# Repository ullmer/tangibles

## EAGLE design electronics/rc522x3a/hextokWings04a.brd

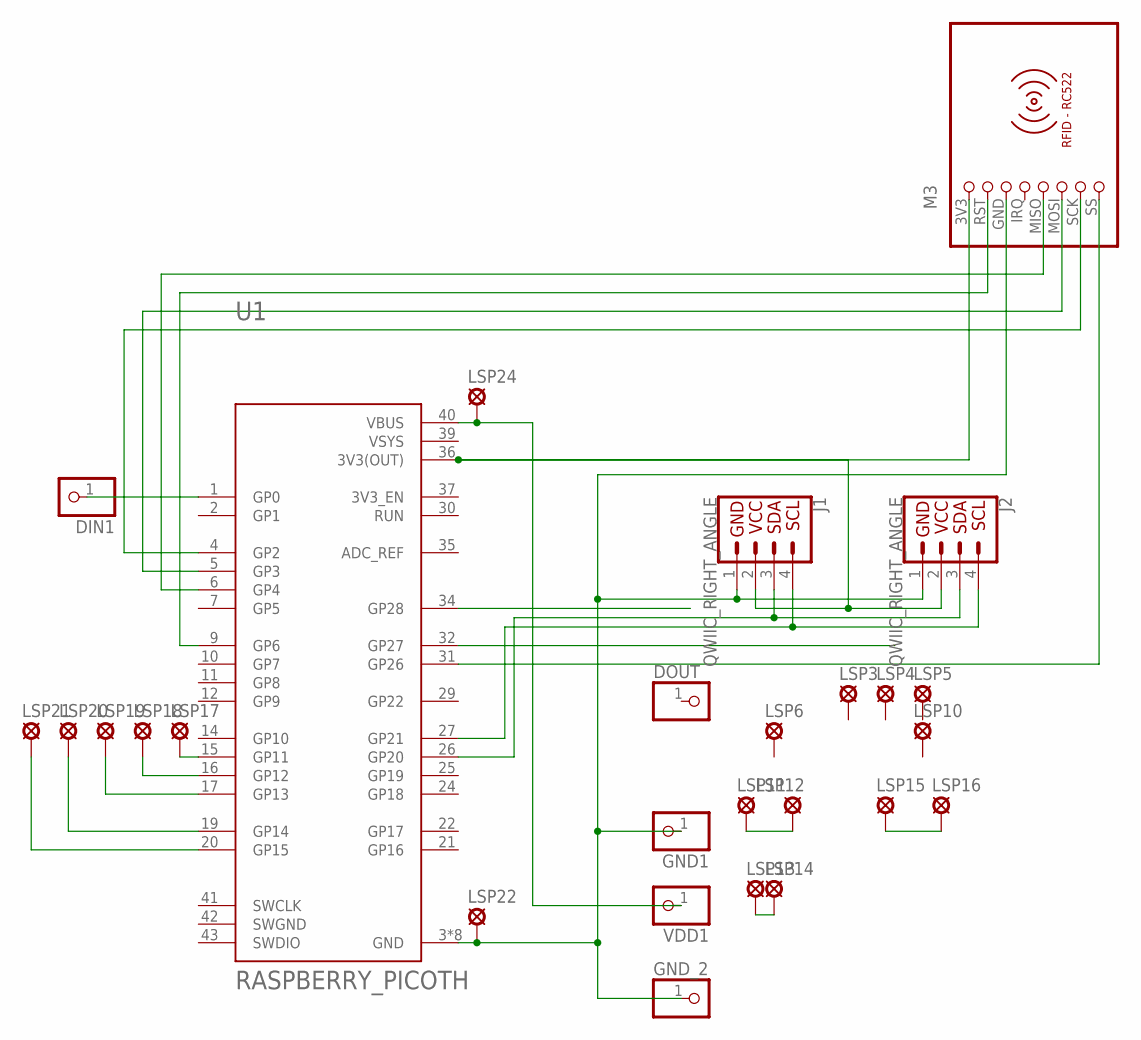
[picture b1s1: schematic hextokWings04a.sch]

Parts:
DIN1: PINHD-1X1CB; 1X01-CLEANBIG
DOUT: PINHD-1X1CB; 1X01-CLEANBIG
GND1: PINHD-1X1CB; 1X01-CLEANBIG
GND_2: PINHD-1X1CB; 1X01-CLEANBIG
J1, J2: QWIIC_RIGHT_ANGLE; JST04_1MM_RA
LSP3, LSP4, LSP5, LSP6, LSP10, LSP11, LSP12, LSP13, LSP14, LSP15, LSP16, LSP17, LSP18, LSP19, LSP20, LSP21, LSP22, LSP24: LSP10
M3: RFID-RC522
U1: RASPBERRY_PICOTH; PICO-PKG-TH
VDD1: PINHD-1X1CB; 1X01-CLEANBIG

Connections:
unnamed: J1.2, J2.2, M3.3V3 (1), U1.36 (3V3(OUT))
unnamed: M3.MOSI (6), U1.5 (GP3)
unnamed: M3.SCK (7), U1.4 (GP2)
unnamed: M3.RST (2), U1.9 (GP6)
unnamed: M3.SS (8), U1.31 (GP26)
unnamed: DIN1.1, U1.1 (GP0)
unnamed: LSP24.MP, U1.40 (VBUS), VDD1.1
unnamed: M3.MISO (5), U1.6 (GP4)
unnamed: LSP11.MP, LSP12.MP
unnamed: LSP13.MP, LSP14.MP
unnamed: LSP15.MP, LSP16.MP
unnamed: LSP17.MP, U1.15 (GP11)
unnamed: LSP18.MP, U1.16 (GP12)
unnamed: LSP19.MP, U1.17 (GP13)
unnamed: LSP20.MP, U1.19 (GP14)
unnamed: LSP21.MP, U1.20 (GP15)
unnamed: J1.3, J2.3, U1.26 (GP20)
unnamed: J1.4, J2.4, U1.27 (GP21)
unnamed: GND1.1, GND_2.1, J1.1, J2.1, LSP22.MP, M3.GND (3), U1.3 (GND), U1.8 (GND), U1.13 (GND), U1.18 (GND), U1.23 (GND), U1.28 (GND), U1.33 (GND), U1.38 (GND)
SWGND: U1.42 (SWGND)
VSYS: U1.39 (VSYS)

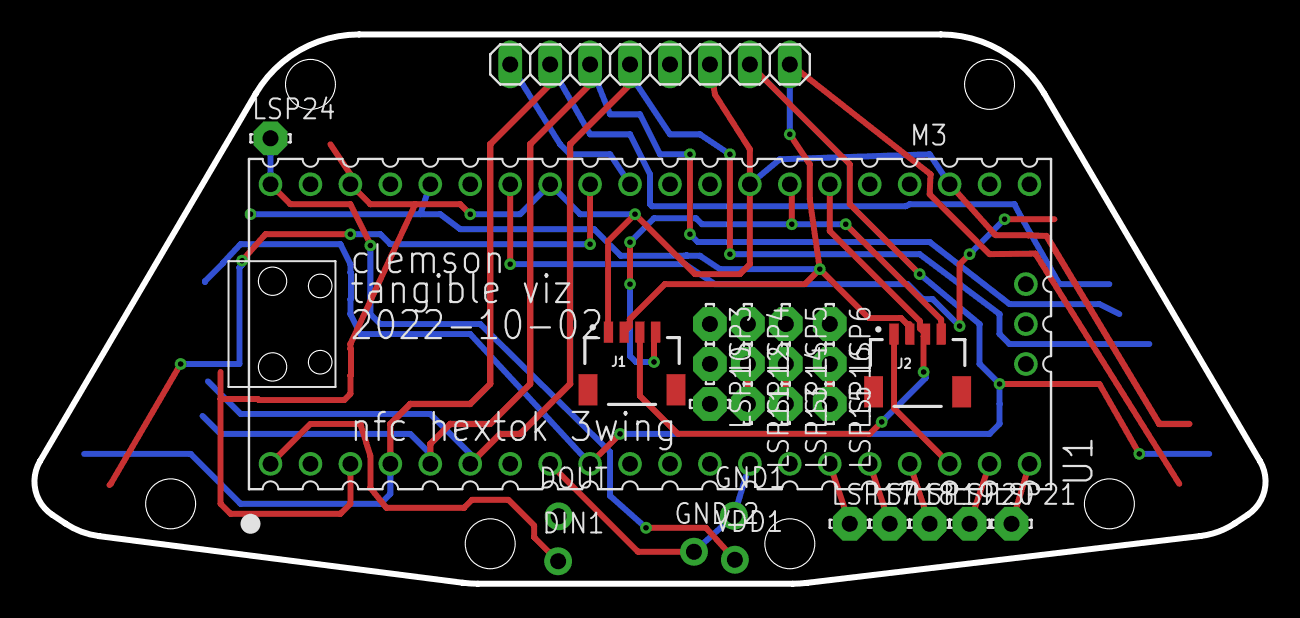
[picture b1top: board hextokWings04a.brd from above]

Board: 2 copper layers, 78.3 x 34.9 mm, 27 parts (0 on the bottom side), 19 nets.

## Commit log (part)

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2025-05-09 moving to exploratory directory, about to rework
2025-05-09 test
2025-05-09 class-descendant evolution
2025-05-09 debugging
2025-05-10 progress
2025-05-10 working
2025-05-12 repeating animation
2025-05-12 seems to be operable
2025-05-12 animated scaling in pygame zero functional. (position settings likely need evolution)
2025-05-12 working to update constructor
2025-05-12 progress with constructor, though seems to break animation
2025-05-12 seems to fix constructor
2025-05-12 seems to fix enoActorScaled constructor
2025-05-13 beginning to add more slider handling
2025-05-14 moving run code to separate file
2025-05-17 Copilot-generated code; untested, migrating between machines to test
2025-05-19 iteration, not yet working
2025-05-19 iterating
2025-05-19 progres
2025-05-19 example aggregations
2025-05-21 debugging midi IDs on an Ubuntu machine (rather than prior win10)
2025-05-21 tweaks
2025-05-21 rect tweak
2025-05-21 Copilot-generated scripts for AVX2 support; seemed to realize ~50% performance acceleration for large Surfaces on an MS Surface Book 2
2025-06-08 port begins
2025-06-08 stub
2025-07-17 warmup
2025-07-17 bau refactoring, mostly layout
2025-07-17 neotrellis entry by copilot, reformatted by bau
2025-07-17 prolog representation of corresponding yaml file
2025-07-17 reminder of package installation
2025-07-17 decimal variations
2025-07-17 visual restructuring
2025-07-17 partitioning underway
2025-07-17 separation of data/facts from transformation/rules
2025-08-21 adding new base class for error management, etc.
2025-08-21 error handling
2025-08-21 different source
2026-01-22 POEMS (Physical Objects with Embedded Memories): Ullmer & Glos, 1995
2026-01-22 Organizational Relations: Brygg Ullmer (fusion of U. Illinois & Interval Research, 1993)
2026-01-22 media browser content (migrated from designThinking)
2026-02-07 small refactoring of mbrowser03.py
2026-02-07 eliminating global
2026-02-27 animation iterations
2026-03-07 first steps]
2026-03-07 first partial pass
2026-03-07 expanded
2026-03-07 Prolog mapping by CoPilot
2026-03-07 fixes
2026-03-07 refactored for plurality of components
2026-03-07 discretizing
2026-03-07 HiLetGo RFID RC522
2026-03-07 HiLetGo RFID-RC522 module Prolog (shadowing equiv YAML)
2026-03-08 more recent mods inaccessible; sigh.
2026-03-16 supporting
2026-03-16 symlink
2026-03-16 top shift animation functioning
2026-03-16 import tweak
2026-03-16 backdrops
2026-03-16 removing temp, sigh
2026-03-16 context on anchors and aliases within YAML
2026-03-17 swiftly evolving
2026-03-17 refactoring
2026-03-17 validation hack
2026-03-18 separating trusted from potentially untrusted elements
2026-03-18 iterations
2026-03-18 first documentation pass
2026-03-18 Update enoPrismsDetails.md — removing more v3s
2026-03-19 tweaking back 03
2026-03-21 replicating 04, beginning to integrate enoPrismsDetails
2026-03-24 Image source (copyright-cleared) and Photoshop 2025-derived variant
2026-03-24 figures and themes toward example
2026-03-24 populating
2026-03-24 renaming, re greater complexity of startup++
2026-03-24 placeholder
2026-03-25 first test
2026-03-25 yaml to prolog transformers
2026-03-25 extending to handle both people and themes
2026-03-25 renaming
2026-03-25 people & themes
2026-03-25 segmenting code
2026-03-25 segmenting, about to wrap into a class
2026-03-25 comment typehinting, in anticipation of mixins
2026-03-25 adding comment typehints
2026-03-25 Enodia people+themes yaml+pgz mixin-augmented classes
2026-03-25 renaming interim
2026-03-25 commented inherited|mixedin fields and methods
2026-03-25 beginning to populate
2026-03-25 try/except
2026-03-25 augmenting
2026-03-25 name abbreviations
2026-03-25 removing
2026-03-25 glyphs
2026-03-25 animation example in class
2026-03-25 moving
2026-03-25 iteration
2026-03-25 100px
2026-03-25 illustrating beginning of abstraction
2026-03-25 another import required
2026-03-25 replicating 06
2026-03-26 migrating code from designThinking github
2026-03-26 testing for presence of file
2026-03-27 100pix -> 80pix
2026-03-27 move
2026-03-27 hacky as expressed, but...
2026-03-27 formatting
2026-03-27 tweaks, partly per caching
2026-03-27 rename
2026-03-27 changed order of mixin term
2026-03-27 populated
2026-03-27 2D matrix
2026-03-27 comment
2026-03-27 moving backdrops, people glyphs
2026-03-27 removing; variants replaced under people/
2026-03-30 tweak
2026-03-31 cache progress
2026-03-31 progress, contemplating refactoring
2026-03-31 evolution of enoOSsupport.py by BAU and copilot
2026-03-31 proto-documentation
2026-03-31 staging in copilot-suggested integrations of enoRemoteContent toward TLS++ navigation
2026-03-31 renaming to reflect evolving content
2026-04-01 migrated downloading functionality to enoRemoteContent.py
2026-04-01 phasing in trust modulation
2026-04-01 more integrated
2026-04-01 may be working on insecure content!
2026-04-01 check if already cached
2026-04-01 button array test restaging
2026-04-01 earlier
2026-04-03 git:plasma/libEnodia/python modules
2026-04-03 menu glyphs
2026-04-08 moving location
2026-04-08 relocating source modules
2026-04-08 copy of py/senetEth07.py amidst reorg
2026-04-08 adding comment to ~opaque first line
2026-04-08 debugging module paths
2026-04-08 copying from plasma:libEnodia/python/tests/yaml
2026-04-09 AtaBase -> EnoBase
2026-06-01 Adafruit KB2040 mapping
2026-06-01 working to resolve earlier hallucinations
2026-06-01 evolving proto representation
2026-06-01 replication of mbrowser.02, toward renaming ataBase -> enoBase
2026-06-01 refactoring ataBase -> enoBase
2026-06-01 replicating mbrowser.02 yaml files
2026-06-01 tweaking
2026-06-04 stubs
2026-06-04 copying from ../mbrowser.03

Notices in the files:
parts and their libraries:
SparkFun-Connectors: Licensing: Creative Commons ShareAlike 4.0 International - https://creativecommons.org/licenses/by-sa/4.0
